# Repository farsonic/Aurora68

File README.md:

# Aurora68

A Raspberry Pi on a PiStorm in a compact Macintosh's 68000 socket. It runs Emu68 and boots Apple's Macintosh
IIci ROM, so the SE becomes a 68040-class Mac with up to 128 MB of memory, while its own screen, keyboard, mouse,
floppy and SCSI keep working. On top it adds a colour second screen and stereo sound over HDMI, disk images on the
SD card, WiFi, Ethernet, Bluetooth and USB keyboards and mice, USB sticks and a remote control, through a NuBus
card that exists only in software.

- **Macs:** the SE; the Plus, 512Ke, 512K and 128K with `mac.board=plus|512ke|512k|128k`.
- **Systems:** System 7.1 and System 6.0.8 tested. A/UX 3.1.1 runs on a real SE with the experimental 68030 MMU
  (`mac.mmu=full`), with Bluetooth and USB input, networking over the Pi's WiFi and the HDMI screen: see
  `docs/25-aux-handover.md`.
- **Hardware:** a classic PiStorm (the DIP-64 Amiga board) with a Raspberry Pi 3A+ or Zero 2 W (they fit), or a
  3B/3B+ (overhangs), and a microSD card with a FAT32 first partition.
- **You supply:** your own Macintosh IIci ROM (368CADFE, 512 KB) and Mac system software. Nothing of Apple's is
  included.

## Quick start

1. Unzip the latest release from the Releases page onto the card's root.
2. Copy your IIci ROM there as `MacIIci_368CADFE.rom`.
3. In the card's root (macOS or Linux, needs `curl` and `python3`), run this one line. It fetches the Pi's boot
   files and every Pi model's WiFi and Bluetooth firmware, checks them, and builds the container `aurora68.cpio`:

   ```bash
   sh get-firmware.sh --container MacIIci_368CADFE.rom --declrom aurora68-se.declrom
   ```

4. Put the card in the Pi, the PiStorm in the 68000 socket (pin 1 at the notch end), plug in an HDMI monitor if
   you have one, and switch on. `cmdline.txt` as shipped is ready for an SE:

   ```
   enable_cache debug mac.board=se bt.pair=1 mac.console=hdmi
   ```

The Mac starts from its own SCSI disk (or a BlueSCSI), a floppy, or a disk image (`.img`, `.hda`, `.dsk`) in the
card's root. The Aurora68 programs come on `Aurora68-Apps.img`, which the Mac mounts as the disk "Aurora68" beside
your startup disk; the drivers need no installing.
`READ-ME-FIRST.txt` in the zip says what the first start should look like.

## More

- `docs/guide.md`: the full guide. Every `cmdline.txt` option, `config.txt` and HDMI sizes, disks and SCSI images,
  the other Macs, the remote control, Setup and Recovery, larger startup disks, the hardware table.
- `RELEASE-NOTES.md`: what is new, and what has been checked on real hardware.
- `docs/00-overview.md`: the story of the project, with links to the working documents.
- `CLAUDE.md`: building everything from source and running the QEMU/MAME testbed.

## Licences

The Emu68 fork is MPL-2.0, the Alice68 modules in `emu68/src/alice/` are GPL-2.0-only, and the Macintosh side,
tools and documents are MPL-2.0. Third-party code compiled into the kernel (minimp3, dr_flac, stb_vorbis) and the
radio stations Aurora68 Play lists are credited in `docs/guide.md`, "Licences". Apple ROMs, system software and
Broadcom's firmware are not distributed.

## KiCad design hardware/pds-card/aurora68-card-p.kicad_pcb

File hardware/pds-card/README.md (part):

<!-- SPDX-License-Identifier: MPL-2.0 -->
# Aurora68 Card P: a Raspberry Pi 3A+ in the Macintosh SE's processor direct slot

*24 November 2026, first draft; reworked twice on 25 November 2026 (first the CPLD beside the Pi's header, the Pi 3B/3B+ keep-out
widened, 3D models; then the Pi beside the slot plug, with the CPLD, latches and switches between;
the owner's 30 mm blower on a Raspberry Pi 5-style fan header; /BR held and stock mode from the Interrupt switch, after
the MicroMac Performer).* A KiCad 8 design for **Card P** of docs/22 section 5.1: a card for the SE's 96-pin
processor direct slot (PDS) that carries a Raspberry Pi 3A+ on its 40-pin header and does what the classic PiStorm
does in the 68000's socket, through the slot instead. The SE's own 68000 stays in its socket; the card takes the
bus from it with /BR, /BG and /BGACK and can hand it back ("stock mode"). The Pi runs Aurora68's kernel unchanged:
the card speaks the classic PiStorm's GPIO protocol (`PROTOCOL.md`). The bus half (CPLD, latches, bus switches,
power, slot plug) and the Pi now sit together in the right-hand 80 mm of the card, beside the slot plug; a Compute
Module card (Card M) would reuse that corner with a module in the Pi's place.

## Status: a draft for a hardware designer to review

- **Not reviewed** by anyone who builds hardware. **Not built.** **KiCad's ERC and DRC have not been run**: KiCad
  is not installed where the files were made. They were generated by Python from `tools/design.py`, read back
  and checked by `tools/validate.py` (below), which is no substitute.
- **Four layers since 25 November 2026, and not fully routed** (see "Routing"): Freerouting leaves 40 connections open in 25 nets (the data latches' slot side, SE_D1-D15; nine of the Pi's data lines to the latches; two latch strobes); the
  copper is a starting point for a person.
- **The CPLD logic is simulated, not synthesised**: Icarus Verilog against a behavioural SE, 1608 checks pass and
  four deliberately broken copies fail (`rtl/README.md`); Quartus has not fitted it, so whether it fits an EPM240 is
  an estimate (145 LUTs and 117 flip-flops by yosys: probably yes; the board takes an EPM570 in the same footprint).
- Several mechanical facts are our reading of Apple's drawings and need a real SE with its chassis and a ruler:
  the height limit's direction, the plug's exact position, the Pi's stack (sections below).

## What is on the card

| Ref | Part | Why |
|---|---|---|
| J1 | 96-pin DIN 41612 type C plug, male, straight, press-fit, **on the underside** | the slot (Apple, *Designing Cards and Drivers*, 3rd ed., Figure 17-4) |
| U1 | EPM240T100C5N (or EPM570T100C5N), as the PiStorm | the bus cycle, arbitration, stock mode, fan, status (`rtl/aurora68_pds.v`) |
| U2-U5 | 74LVC16373 x4, as the PiStorm | address (A1-A23) and data latches, write and read, 5 V tolerant |
| U6, U7 | SN74CBTD3384 x2, as the PiStorm | the strobes, function codes, /DTACK, /VPA, /BERR, E, /VMA, interrupts, /RESET and the arbitration lines between the slot and the CPLD (one channel spare since /PMCYC went) |
| U8 | AMS1117-3.3 (the PiStorm's LM1117-3.3) | 3.3 V for the CPLD and latches |
| F1, U9 | 1.1 A polyfuse, LM66100 ideal diode | the slot's +5 V to the Pi and the card; a Pi also powered from its own USB never feeds the SE |
| J2 | 2x20 socket, 6.0 mm | the Pi 3A+ (or Zero 2 W), plugged in components-down |
| J3, R8, D1, R6, F2 | JST-SH 4-pin fan header (SM04B-SRSS-TB) wired as the Raspberry Pi 5's FAN connector, 100 ohm from the CPLD's PWM pin, a BAT54C holding PWM and TACH at 3.3 V, the tachometer pull-up, a 0.35 A polyfuse | docs/22 section 6; section "The fan" |
| M1 | the owner's 30 x 30 x 7 mm 5 V blower, optional, on three M2 screws | section "The fan" |
| J4, F3, R11 | 10-way 1.0 mm FFC connector, 0.75 A polyfuse | the cable to a connector card at the rear (Apple's Figures 17-2, 17-7, 17-8): USB, +5 V for it, an LED |
| J5 | 4-pin header | USB from the Pi 3A+'s USB-A socket (a short pigtail with a **right-angle** plug, its cable towards the rear: section "The fan"), on to J4. Its VBUS pin is deliberately not connected |
| D2, R10 | LED | activity |
| R1-R5, C1-C16 | as the PiStorm where it has them | JTAG pull-ups (4.7 k on TMS and TDI), 22 ohm on the 68000 clock C8M (R3), the SE power sense (10 k / 15 k), decoupling |
| R12 | 22 ohm | GPCLK0's series resistor at the source, beside the Pi's pin 7 (new on 25 November) |
| H1, H2 | 3.86 mm holes | Apple's card supports (Figure 17-1) |
| H3-H8 | M2.5 holes | the Pi's standoffs (3A+: four; Zero 2 W: two more) |

The full list with values, LCSC numbers where known, heights and notes is `bom.csv`. The netlist is the
schematic: `aurora68-card-p.kicad_sch` and its five sheets (slot and bus switches, CPLD and latches, Pi socket,
power, fan/LED/rear cable), pictured in `img/sch-*.png`. There is no stock-mode jumper any more: stock mode is
entered with the SE's own Interrupt switch held through a reset (section "Arbitration and stock mode").

## How it follows the PiStorm, and where it departs

The owner's rule for Card P: as simple and as close to the PiStorm Rev B as possible, cheap to make. So the
circuit is the Rev B's (reference/pistorm: `Pistorm_Rev_B-1.pdf`, the Altium files, the BOM): the same CPLD family
and package wired the same way for an EPM240 or EPM570, the same four 74LVC16373 latches, the same two CBTD3384
bus switches carrying the same 68000 control signals, the 22 ohm resistor on the CPU clock, the 3.3 V LDO with
22 uF in and out, 4.7 k pull-ups on TMS and TDI, 100 nF per IC, the Pi's GPIO 0-27 used exactly as there, the Pi
plugged in components-down over the card as it hangs over the logic board on a PiStorm, and **every CPLD pin of
every signal the PiStorm has on the PiStorm's own pin number** (`rtl/aurora68_pds.qsf`, checked against the Rev B's
`pistorm.qsf`; the Pi header's nets checked against the Rev B schematic by reading its Altium file). Departures,
each for a reason:

| # | Departure | Reason |
|---|---|---|
| 1 | A 96-pin DIN plug on the underside instead of the 68000 DIP-64 plug | the slot |
| 2 | CPLD pin 53 (E) is an input, 71 (/BG) an input, 69 (/BR) and 70 (/BGACK) open-drain outputs; 68 (the PiStorm's /HALT), 51, 99, 100 (CLK_SEL, C1, C3) unused; new: 77 SE power sense, 78 fan PWM, 81 tachometer, 83 LED | the slot card's roles are the other way round: the 68000 is still there, so the card requests the bus instead of granting it and follows the 68000's E; on the SE /HALT is /RESET, so its pin is free |
| 3 | The read timing needs **transparent** latches (74LVC16373) | the new cycle opens the read latch on /DTACK and closes it where a 68000 latches (docs/18 C2). Note: the Rev B BOM in reference/pistorm lists SN74LVC16374 (edge-triggered) although the archive is named "..._74LVC16373": with a '16374 this card would latch at the wrong edge |
| 4 | +5 V through a polyfuse and an LM66100 ideal diode (the PiStorm takes the socket's 5 V straight) | the brief: a Pi on its own USB must not back-feed the SE. A Schottky is simpler but drops 0.35-0.45 V at the Pi's current, putting a Pi 3A+ at or under its 4.63 V under-voltage threshold on an old SE supply (docs/12, "Power through the socket"); a single P-MOSFET with its gate grounded blocks reverse polarity but conducts both ways once on, so it does not stop back-feeding. The LM66100 is one SC-70 part |
| 5 | CBTD3384 VCC from the protected 5 V (5V_PI) | the switches must be off when the card is unpowered, and powered whenever the CPLD is |
| 6 | VCCINT tied to 3.3 V directly | the PiStorm links it through a 0 ohm resistor beside an unfitted 1.8 V regulator option; only MAX II "G" parts would need it |
| 7 | 0603 resistors and capacitors, 0805 for 10 and 22 uF (the PiStorm uses 0402 and 0603) | the owner's assembly preference |
| 8 | Added: the SE power sense (2 resistors), the fan header (wired as a Raspberry Pi 5's: no driver, PWM straight from the CPLD), the FFC to the rear connector card with its fuse, the USB-in header, the activity LED | docs/22 sections 4 and 6 |
| 9 | Not a departure from the PiStorm but from the brief: the slot's control signals reach the CPLD through the CBTD3384 switches, not through 74LVC buffers | the owner's rule. Apple asks for buffering when a card loads a line with more than two 74LS inputs and 30 pF, or more than about 2 inches of trace. Each control line here sees one CMOS input (the CPLD, about 10 pF and 10 uA), the switch (10-12 pF on) and the track on both sides of the switch: a few uA of DC load against two LS loads' 40 uA / 0.8 mA, but a capacitance close to Apple's 30 pF (section "Placement" has the routed figures; on four layers a 0.15 mm track 0.21 mm over its plane is about 0.07 pF/mm). 74LVC buffers near J1 are the remedy if a reviewer or a scope says so. Address and data go through the latches, which are real buffers. The CBTD's level shifting brings 5 V signals down to about 4.3 V at the CPLD (the PiStorm runs that way; the MAX II's absolute maximum input is 4.6 V) |
| 10 | R12, 22 ohm in series with GPCLK0 (GPIO 4) at the Pi's pin | asked for with the placement rework: source termination for the 200 MHz clock. The PiStorm wires GPIO 4 straight to the CPLD; fit 0 ohm to match it. It is the only schematic change of the rework |
| 11 | The CPLD, two latches and both switches sit under the Pi, the Pi beside the slot plug | as on the PiStorm, where the Pi sits over the CPLD and latches: short Pi-speed lines and short SE lines (section "Placement") |
| 13 | Four layers (the PiStorm has two): L1 signals, L2 ground, L3 3.3 V, L4 signals | the owner's choice on 25 November 2026, after two layers left some 50 connections the router could not make: "I don't mind 4 layer if it is simpler to route and produce" (section "The board") |
| 12 | The card holds /BR for as long as it owns the bus, and stock mode is entered with the SE's Interrupt switch held through a reset; /PMCYC is not connected | the MicroMac Performer, a shipped card that took the bus from this slot, worked that way (docs/22 section 10); it removed a jumper and its pull-up (section "Arbitration and stock mode") |
0.4 pF/cm for a 0.15 mm trace over the ground pour, so some 7 pF, plus the switch's 10-12 pF and the CPLD pin's 8-10
pF, about 25-30 pF in all against Apple's 30 pF (C8M, with 20 pF allowed and no switch, sees about 16 pF). That is at
the limit: the reviewer's to confirm, with 74LVC buffers near J1 as the remedy (section "Placement"). Address and data go through the latches, which are real buffers. The CBTD's level shifting brings 5 V signals down to about 4.3 V at the CPLD (the PiStorm runs that way; the MAX II's absolute maximum input is 4.6 V) |

## Placement (25 November 2026)

**The rule this follows.** On the PiStorm the latches sit on the Pi's data bus and their strobes are combinational
copies of the Pi's write and read strobes, so the latches, as well as the CPLD, run at Pi speed; their other side is
the 68000's bus. The first draft put the CPLD and latches by the slot plug, far from the Pi; the 25 November rework
put the CPLD by the Pi, and the Pi-speed lines to the latches grew to 26 cm. With the Pi itself beside the slot plug
both sides are short, with no extra parts. So:

- **The Pi 3A+ sits beside J1**, components down on its socket as before, its microSD end (u = 0) at x = 198.7: as
  close to J1 as its standoffs allow (its u = 3.5 holes end at x = 197.95, J1's courtyard starts at 198.04; further
  right they would land in J1's pin field). It covers x 133.7-198.7, y 53.2-109.2.
- **Turned over about its short axis** this time, so that a 3B/3B+'s USB and RJ45 and their plugs reach away from
  J1, to the empty left of the card: its header now runs along the Pi's **rear** edge (y 55.4/58.0, x 142.1-190.3)
  and its USB socket faces left.
- **The cost of that turn: the HDMI and audio jacks now overhang the card's front edge.** They stand 1.4 and 2.5
  mm past the Pi's own edge (Raspberry Pi's drawing), and the Pi's front edge is at y 109.2 because its rear edge
  cannot come forward of y 53.2 (there Apple's slope allows 9.91 mm and the Pi's back is at 9.90). So the audio jack
  stands 1.6 mm, the HDMI socket 0.5 mm and the micro-USB socket 0.2 mm past Apple's outline at the front, at 2.0 to
  8.5 mm above the card. The alternative, the jacks inside the outline, puts the Pi's rear edge at y 51.6 and its back
  0.15 mm over the slope. Nothing else changes between the two; the owner should choose after measuring what is in
  front of the card's edge in a real SE (the logic board's front part, the SIMMs). `validate.py` reports it as warning
  9e. The HDMI socket now faces the front of the machine, so it is no use for a second screen without a short
  right-angle adaptor, and was no more reachable before.
- **The cluster between the Pi's header and J1, as tight as the PiStorm's:**
  - U1, the EPM240, under the Pi in the pocket between the keep-outs under its USB socket and its SoC (x 146.8-164.1,
    y 60.2-77.5), rotated 180 degrees so its Pi pins face the header and pin 12 (GPCLK0) faces the Pi's pin 7. Its
    decoupling, the JTAG pull-ups and R12 sit beside it, under the Pi.
  - U2 (A1-A15) and the two CBTD3384 switches, U6 and U7, under the Pi in the column between its SoC and display
    connector keep-outs (x 180.8-190.2), right beside J1's address and control pins. U6 carries E, the interrupts,
    /BERR, /RESET, /AS, /UDS, /LDS (its seventh channel is spare); U7 R/W, /DTACK, the arbitration lines, /VMA, /VPA and the function codes,
    each switch by the plug pins it serves.
  - U3 (A16-A23), U4 and U5 (the data, write and read) behind the Pi's header (y 38.5-51.5), by J1's upper address
    and data pins.
  - The power path (F1, the LM66100, the LDO, F2, F3, R4/R5) in the strip behind them along the rear (y 22-34), the
    5 V reaching the Pi's 5 V pins a few cm away.
- **The rest:** the blower M1 left of the Pi with its outlet towards it, its JST-SH header J3 (with R8, D1, R6)
  behind it, all outside the 3B zone but the fan itself (section "The fan"); USB-in J5 behind the 3B zone; the FFC J4
  where Apple suggests the cable connector (rear middle); the LED by it. The card keeps its full length for Apple's
  support holes; its left 68 mm hold nothing but the holes.

**Lengths and loading (25 November 2026).** Straight lines, from the placement alone: GPCLK0 22.9 mm (J2 pin 7,
R12, the CPLD's pin 12); every Pi-to-CPLD net 27 mm or less; the Pi's data bus from its socket to the farthest latch
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
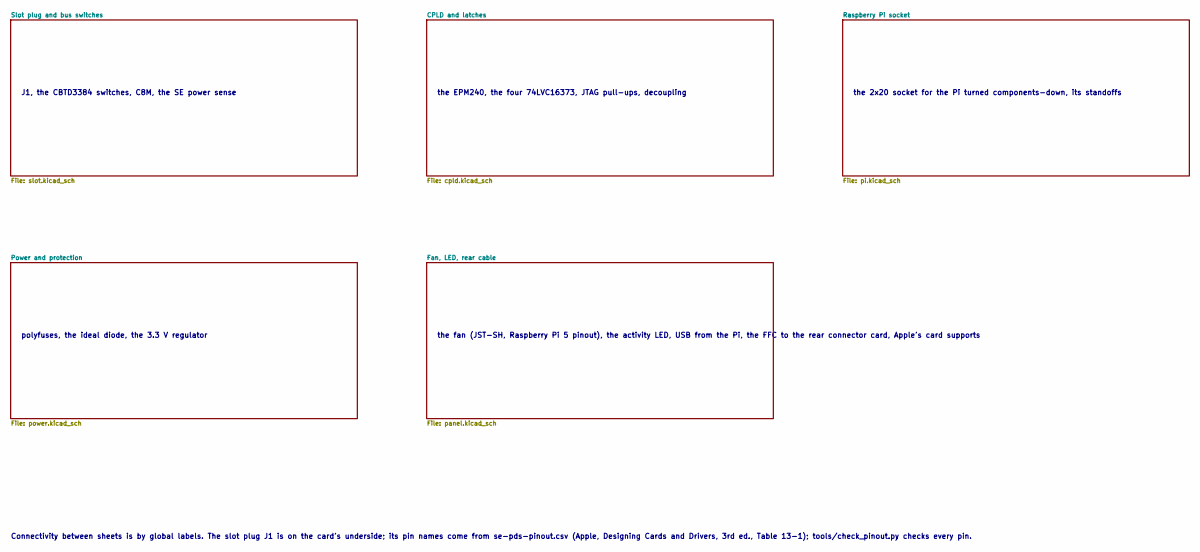
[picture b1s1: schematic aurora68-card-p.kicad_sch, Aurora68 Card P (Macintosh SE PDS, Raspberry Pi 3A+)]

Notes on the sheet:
J1, the CBTD3384 switches, C8M, the SE power sense
the EPM240, the four 74LVC16373, JTAG pull-ups, decoupling
the 2x20 socket for the Pi turned components-down, its standoffs
polyfuses, the ideal diode, the 3.3 V regulator
the fan (JST-SH, Raspberry Pi 5 pinout), the activity LED, USB from the Pi, the FFC to the rear connector card, Apple's card supports
Connectivity between sheets is by global labels. The slot plug J1 is on the card's underside; its pin names come from se-pds-pinout.csv (Apple, Designing Cards and Drivers, 3rd ed., Table 13-1); tools/check_pinout.py checks every pin.

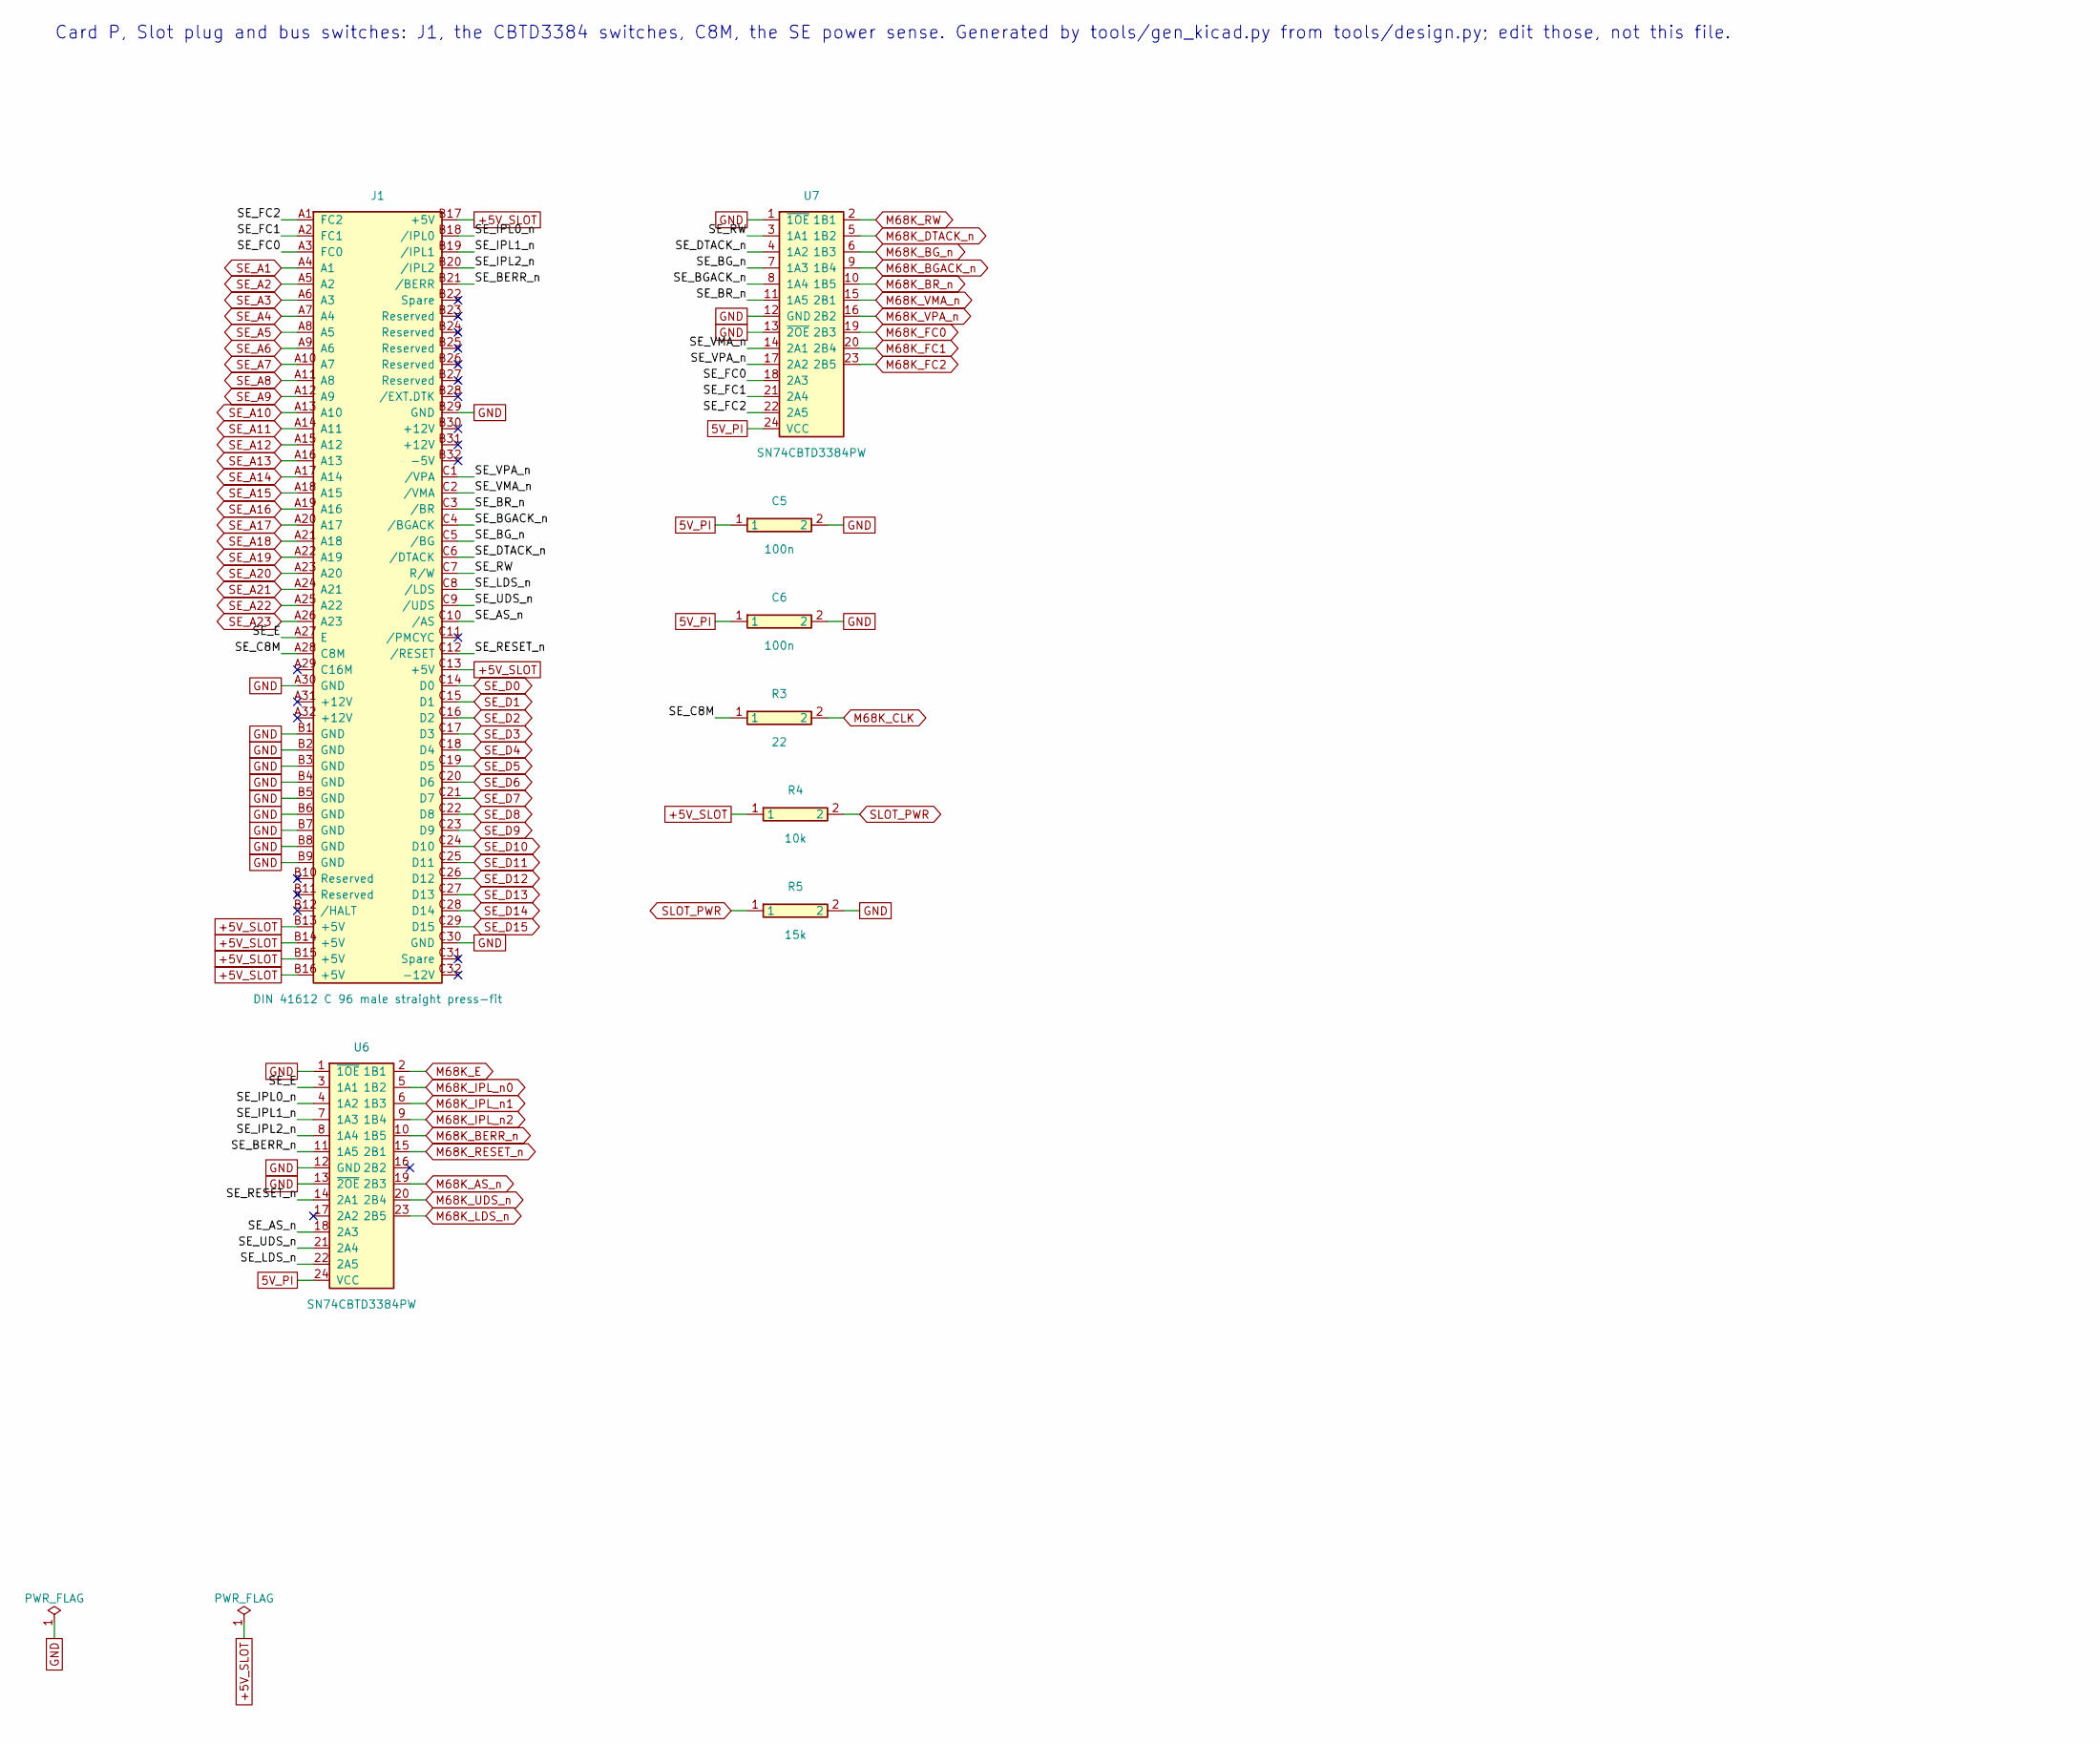
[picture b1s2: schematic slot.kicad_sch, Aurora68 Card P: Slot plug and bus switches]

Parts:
C5, C6: 100n; C_0603_1608Metric; LCSC C14663
J1: DIN 41612 C 96 male straight press-fit; Aurora68_DIN41612_C_3x32_Male_Straight_PressFit_Bottom; MPN DIN 41612 type C, 3x32 (a+b+c), male, s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
R3: 22; R_0603_1608Metric; LCSC C23345
R4: 10k; R_0603_1608Metric; LCSC C25804
R5: 15k; R_0603_1608Metric; LCSC C22809
U6, U7: SN74CBTD3384PW; TSSOP-24_4.4x7.8mm_P0.65mm; MPN SN74CBTD3384PWR; LCSC C7155

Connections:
5V_PI: C5.1, C6.1, U6.24, U7.24; also elsewhere on the board
+5V_SLOT: J1.B13, J1.B14, J1.B15, J1.B16, J1.B17, J1.C13, R4.1; also elsewhere on the board
GND: C5.2, C6.2, J1.A30, J1.B1, J1.B2, J1.B3, J1.B4, J1.B5, J1.B6, J1.B7, J1.B8, J1.B9, J1.B29, J1.C30, R5.2, U6.1, U6.12, U6.13, U7.1, U7.12, U7.13; also elsewhere on the board
M68K_AS_n: U6.19; also elsewhere on the board
M68K_BERR_n: U6.10; also elsewhere on the board
M68K_BGACK_n: U7.9; also elsewhere on the board
M68K_BG_n: U7.6; also elsewhere on the board
M68K_BR_n: U7.10; also elsewhere on the board
M68K_CLK: R3.2; also elsewhere on the board
M68K_DTACK_n: U7.5; also elsewhere on the board
M68K_E: U6.2; also elsewhere on the board
M68K_FC0: U7.19; also elsewhere on the board
M68K_FC1: U7.20; also elsewhere on the board
M68K_FC2: U7.23; also elsewhere on the board
M68K_IPL_n0: U6.5; also elsewhere on the board
M68K_IPL_n1: U6.6; also elsewhere on the board
M68K_IPL_n2: U6.9; also elsewhere on the board
M68K_LDS_n: U6.23; also elsewhere on the board
M68K_RESET_n: U6.15; also elsewhere on the board
M68K_RW: U7.2; also elsewhere on the board
M68K_UDS_n: U6.20; also elsewhere on the board
M68K_VMA_n: U7.15; also elsewhere on the board
M68K_VPA_n: U7.16; also elsewhere on the board
SE_A1: J1.A4; also elsewhere on the board
SE_A2: J1.A5; also elsewhere on the board
SE_A3: J1.A6; also elsewhere on the board
SE_A4: J1.A7; also elsewhere on the board
SE_A5: J1.A8; also elsewhere on the board
SE_A6: J1.A9; also elsewhere on the board
SE_A7: J1.A10; also elsewhere on the board
SE_A8: J1.A11; also elsewhere on the board
SE_A9: J1.A12; also elsewhere on the board
SE_A10: J1.A13; also elsewhere on the board
SE_A11: J1.A14; also elsewhere on the board
SE_A12: J1.A15; also elsewhere on the board
SE_A13: J1.A16; also elsewhere on the board
SE_A14: J1.A17; also elsewhere on the board
SE_A15: J1.A18; also elsewhere on the board
SE_A16: J1.A19; also elsewhere on the board
SE_A17: J1.A20; also elsewhere on the board
SE_A18: J1.A21; also elsewhere on the board
SE_A19: J1.A22; also elsewhere on the board
SE_A20: J1.A23; also elsewhere on the board
SE_A21: J1.A24; also elsewhere on the board
SE_A22: J1.A25; also elsewhere on the board
SE_A23: J1.A26; also elsewhere on the board
SE_AS_n: J1.C10, U6.18
SE_BERR_n: J1.B21, U6.11
SE_BGACK_n: J1.C4, U7.8
SE_BG_n: J1.C5, U7.7
SE_BR_n: J1.C3, U7.11
SE_C8M: J1.A28, R3.1
SE_D0: J1.C14; also elsewhere on the board
SE_D1: J1.C15; also elsewhere on the board
SE_D2: J1.C16; also elsewhere on the board
SE_D3: J1.C17; also elsewhere on the board
SE_D4: J1.C18; also elsewhere on the board
SE_D5: J1.C19; also elsewhere on the board
SE_D6: J1.C20; also elsewhere on the board
SE_D7: J1.C21; also elsewhere on the board
SE_D8: J1.C22; also elsewhere on the board
SE_D9: J1.C23; also elsewhere on the board
SE_D10: J1.C24; also elsewhere on the board
SE_D11: J1.C25; also elsewhere on the board
SE_D12: J1.C26; also elsewhere on the board
SE_D13: J1.C27; also elsewhere on the board
SE_D14: J1.C28; also elsewhere on the board
SE_D15: J1.C29; also elsewhere on the board
SE_DTACK_n: J1.C6, U7.4
SE_E: J1.A27, U6.3
SE_FC0: J1.A3, U7.18
SE_FC1: J1.A2, U7.21
SE_FC2: J1.A1, U7.22
SE_IPL0_n: J1.B18, U6.4
SE_IPL1_n: J1.B19, U6.7
SE_IPL2_n: J1.B20, U6.8
SE_LDS_n: J1.C8, U6.22
SE_RESET_n: J1.C12, U6.14
SE_RW: J1.C7, U7.3
SE_UDS_n: J1.C9, U6.21
SE_VMA_n: J1.C2, U7.14
SE_VPA_n: J1.C1, U7.17
SLOT_PWR: R4.2, R5.1; also elsewhere on the board

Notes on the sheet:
Card P, Slot plug and bus switches: J1, the CBTD3384 switches, C8M, the SE power sense. Generated by tools/gen_kicad.py from tools/design.py; edit those, not this file.

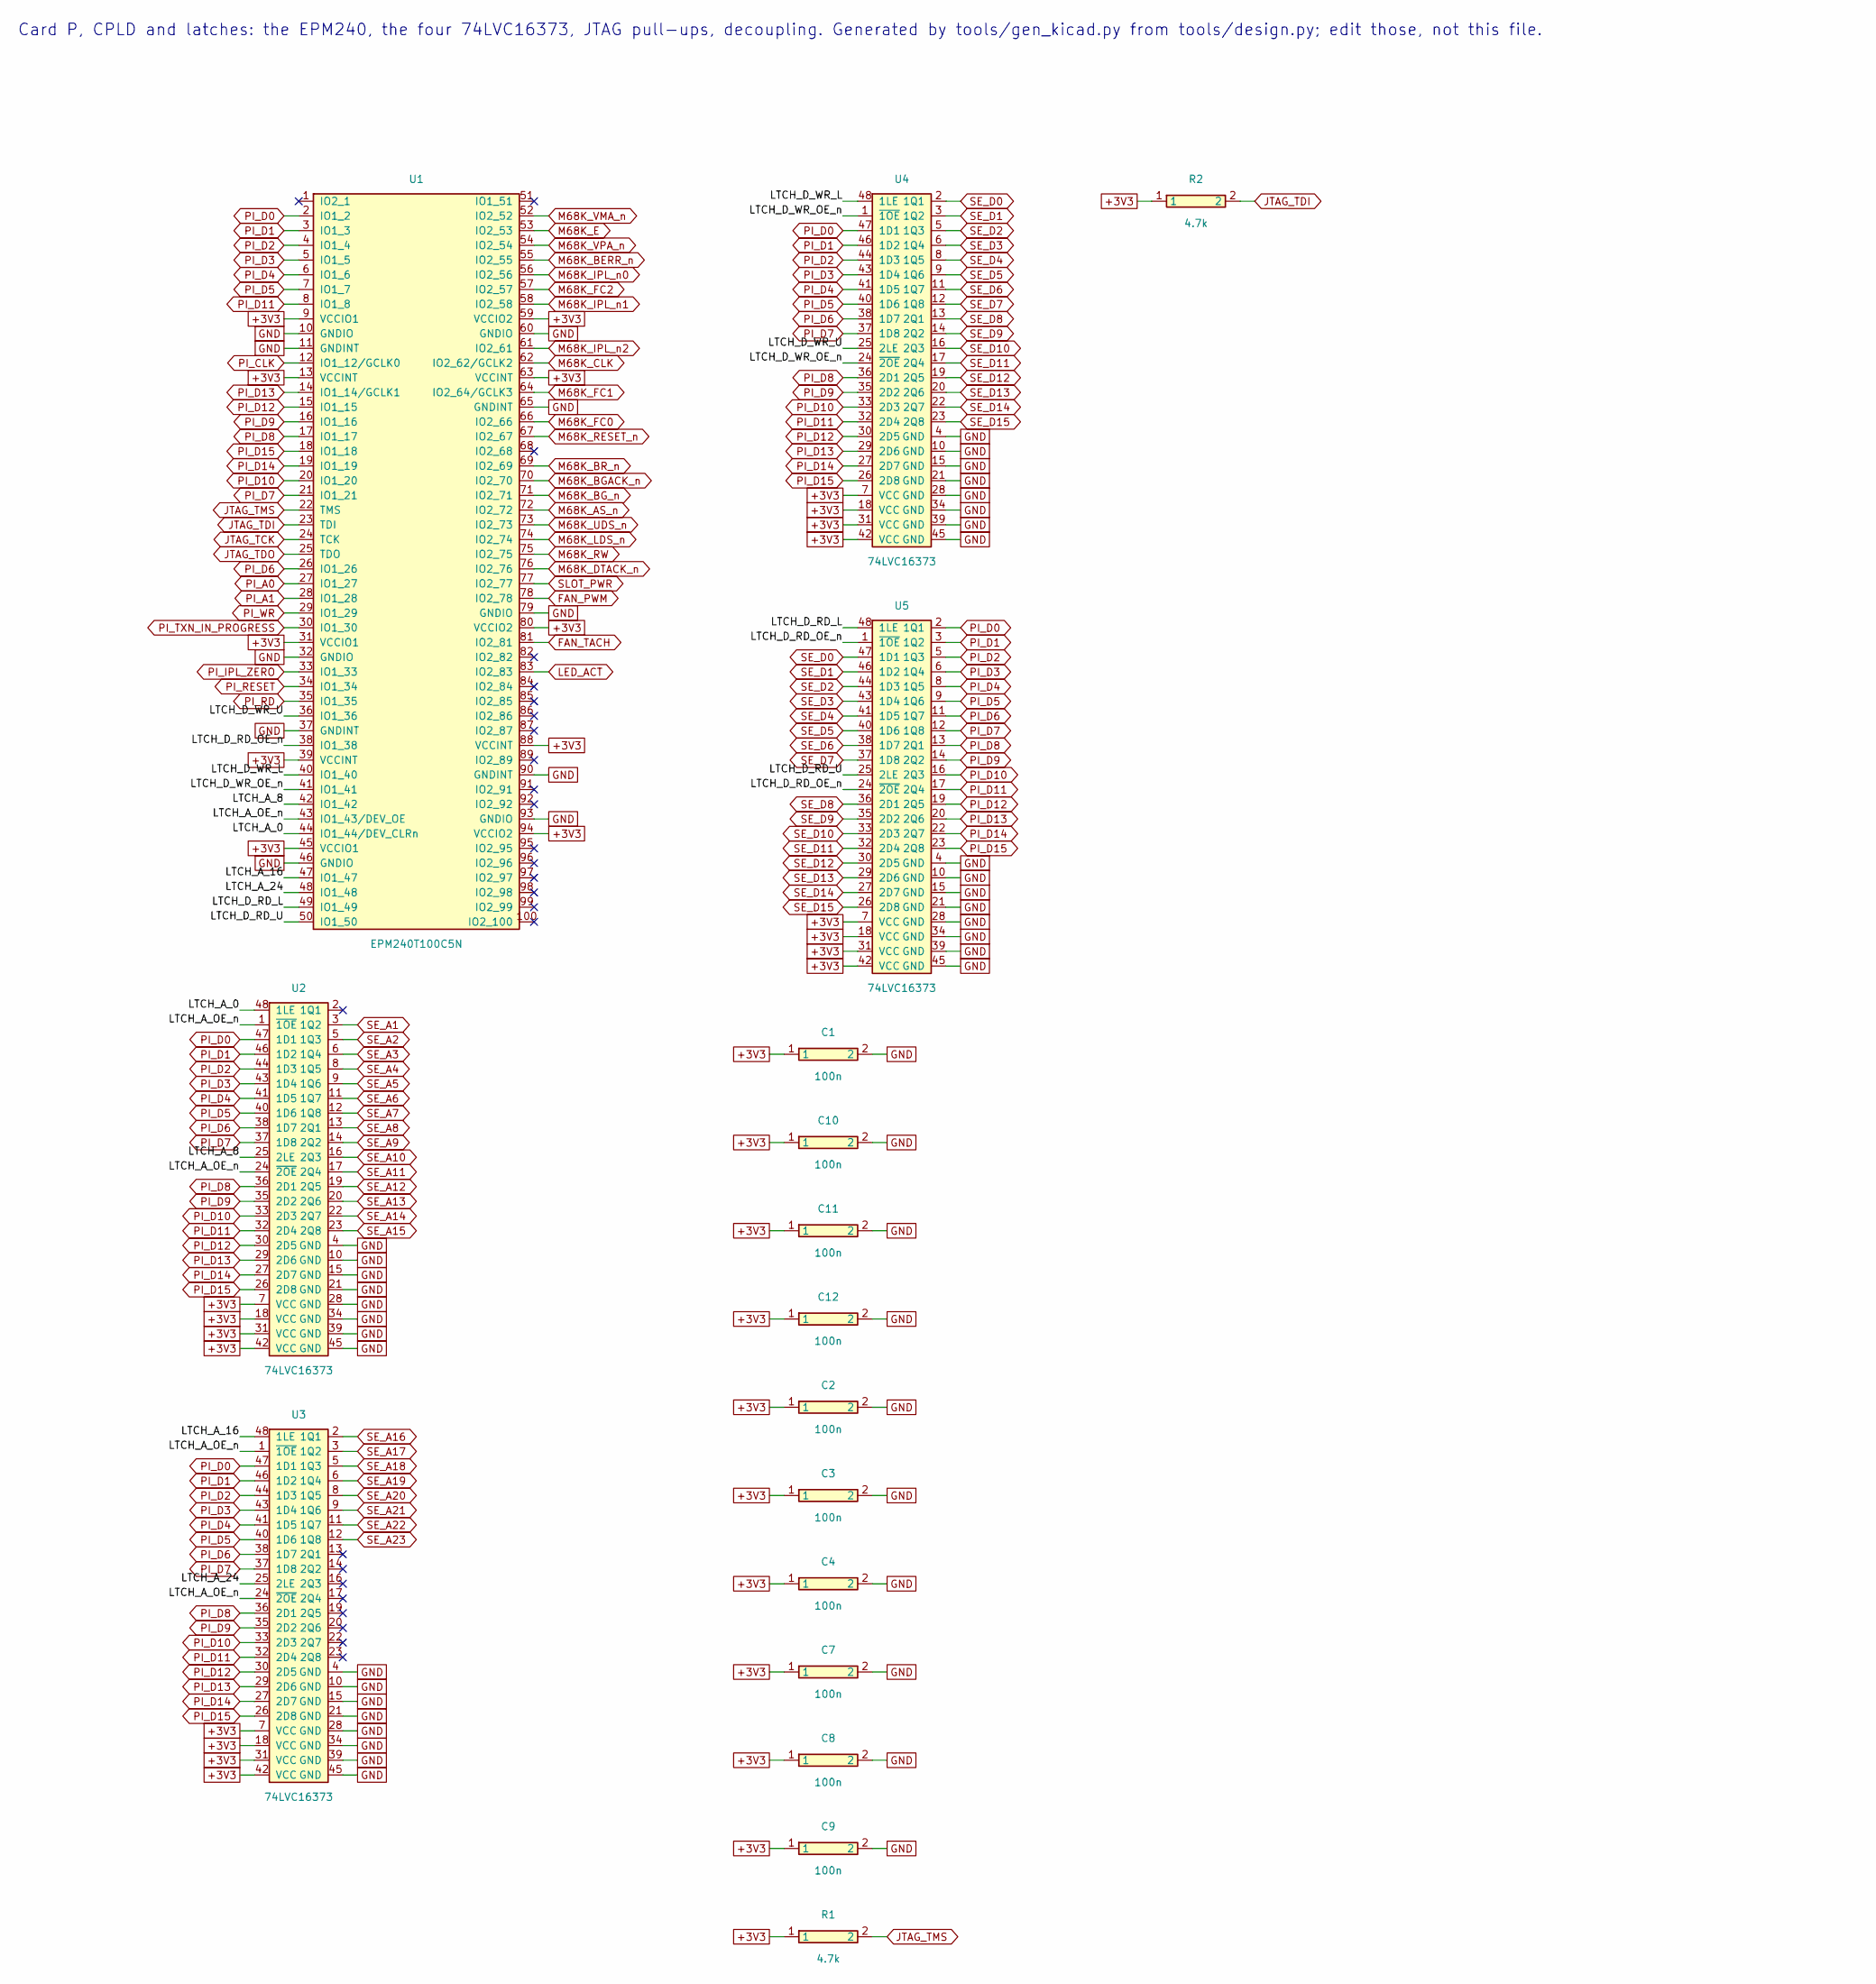
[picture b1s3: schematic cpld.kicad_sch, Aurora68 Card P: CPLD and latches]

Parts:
C1, C2, C3, C4, C7, C8, C9, C10, C11, C12: 100n; C_0603_1608Metric; LCSC C14663
R1, R2: 4.7k; R_0603_1608Metric; LCSC C23162
U1: EPM240T100C5N; TQFP-100_14x14mm_P0.5mm; MPN EPM240T100C5N (or EPM570T100C5N, LCSC C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
U2, U3, U4, U5: 74LVC16373; TSSOP-48_6.1x12.5mm_P0.5mm; MPN SN74LVC16373ADGGR

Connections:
+3V3: C1.1, C2.1, C3.1, C4.1, C7.1, C8.1, C9.1, C10.1, C11.1, C12.1, R1.1, R2.1, U1.9, U1.13, U1.31, U1.39, U1.45, U1.59, U1.63, U1.80, U1.88, U1.94, U2.7, U2.18, U2.31, U2.42, U3.7, U3.18, U3.31, U3.42, U4.7, U4.18, U4.31, U4.42, U5.7, U5.18, U5.31, U5.42; also elsewhere on the board
FAN_PWM: U1.78; also elsewhere on the board
FAN_TACH: U1.81; also elsewhere on the board
GND: C1.2, C2.2, C3.2, C4.2, C7.2, C8.2, C9.2, C10.2, C11.2, C12.2, U1.10, U1.11, U1.32, U1.37, U1.46, U1.60, U1.65, U1.79, U1.90, U1.93, U2.4, U2.10, U2.15, U2.21, U2.28, U2.34, U2.39, U2.45, U3.4, U3.10, U3.15, U3.21, U3.28, U3.34, U3.39, U3.45, U4.4, U4.10, U4.15, U4.21, U4.28, U4.34, U4.39, U4.45, U5.4, U5.10, U5.15, U5.21, U5.28, U5.34, U5.39, U5.45; also elsewhere on the board
JTAG_TCK: U1.24; also elsewhere on the board
JTAG_TDI: R2.2, U1.23; also elsewhere on the board
JTAG_TDO: U1.25; also elsewhere on the board
JTAG_TMS: R1.2, U1.22; also elsewhere on the board
LED_ACT: U1.83; also elsewhere on the board
LTCH_A_0: U1.44, U2.48
LTCH_A_8: U1.42, U2.25
LTCH_A_16: U1.47, U3.48
LTCH_A_24: U1.48, U3.25
LTCH_A_OE_n: U1.43, U2.1, U2.24, U3.1, U3.24
LTCH_D_RD_L: U1.49, U5.48
LTCH_D_RD_OE_n: U1.38, U5.1, U5.24
LTCH_D_RD_U: U1.50, U5.25
LTCH_D_WR_L: U1.40, U4.48
LTCH_D_WR_OE_n: U1.41, U4.1, U4.24
LTCH_D_WR_U: U1.36, U4.25
M68K_AS_n: U1.72; also elsewhere on the board
M68K_BERR_n: U1.55; also elsewhere on the board
M68K_BGACK_n: U1.70; also elsewhere on the board
M68K_BG_n: U1.71; also elsewhere on the board
M68K_BR_n: U1.69; also elsewhere on the board
M68K_CLK: U1.62; also elsewhere on the board
M68K_DTACK_n: U1.76; also elsewhere on the board
M68K_E: U1.53; also elsewhere on the board
M68K_FC0: U1.66; also elsewhere on the board
M68K_FC1: U1.64; also elsewhere on the board
M68K_FC2: U1.57; also elsewhere on the board
M68K_IPL_n0: U1.56; also elsewhere on the board
M68K_IPL_n1: U1.58; also elsewhere on the board
M68K_IPL_n2: U1.61; also elsewhere on the board
M68K_LDS_n: U1.74; also elsewhere on the board
M68K_RESET_n: U1.67; also elsewhere on the board
M68K_RW: U1.75; also elsewhere on the board
M68K_UDS_n: U1.73; also elsewhere on the board
M68K_VMA_n: U1.52; also elsewhere on the board
M68K_VPA_n: U1.54; also elsewhere on the board
PI_A0: U1.27; also elsewhere on the board
PI_A1: U1.28; also elsewhere on the board
PI_CLK: U1.12; also elsewhere on the board
PI_D0: U1.2, U2.47, U3.47, U4.47, U5.2; also elsewhere on the board
PI_D1: U1.3, U2.46, U3.46, U4.46, U5.3; also elsewhere on the board
PI_D2: U1.4, U2.44, U3.44, U4.44, U5.5; also elsewhere on the board
PI_D3: U1.5, U2.43, U3.43, U4.43, U5.6; also elsewhere on the board
PI_D4: U1.6, U2.41, U3.41, U4.41, U5.8; also elsewhere on the board
PI_D5: U1.7, U2.40, U3.40, U4.40, U5.9; also elsewhere on the board
PI_D6: U1.26, U2.38, U3.38, U4.38, U5.11; also elsewhere on the board
PI_D7: U1.21, U2.37, U3.37, U4.37, U5.12; also elsewhere on the board
PI_D8: U1.17, U2.36, U3.36, U4.36, U5.13; also elsewhere on the board
PI_D9: U1.16, U2.35, U3.35, U4.35, U5.14; also elsewhere on the board
PI_D10: U1.20, U2.33, U3.33, U4.33, U5.16; also elsewhere on the board
PI_D11: U1.8, U2.32, U3.32, U4.32, U5.17; also elsewhere on the board
PI_D12: U1.15, U2.30, U3.30, U4.30, U5.19; also elsewhere on the board
PI_D13: U1.14, U2.29, U3.29, U4.29, U5.20; also elsewhere on the board
PI_D14: U1.19, U2.27, U3.27, U4.27, U5.22; also elsewhere on the board
PI_D15: U1.18, U2.26, U3.26, U4.26, U5.23; also elsewhere on the board
PI_IPL_ZERO: U1.33; also elsewhere on the board
PI_RD: U1.35; also elsewhere on the board
PI_RESET: U1.34; also elsewhere on the board
PI_TXN_IN_PROGRESS: U1.30; also elsewhere on the board
PI_WR: U1.29; also elsewhere on the board
SE_A1: U2.3; also elsewhere on the board
SE_A2: U2.5; also elsewhere on the board
SE_A3: U2.6; also elsewhere on the board
SE_A4: U2.8; also elsewhere on the board
SE_A5: U2.9; also elsewhere on the board
SE_A6: U2.11; also elsewhere on the board
SE_A7: U2.12; also elsewhere on the board
SE_A8: U2.13; also elsewhere on the board
SE_A9: U2.14; also elsewhere on the board
SE_A10: U2.16; also elsewhere on the board
SE_A11: U2.17; also elsewhere on the board
SE_A12: U2.19; also elsewhere on the board
SE_A13: U2.20; also elsewhere on the board
SE_A14: U2.22; also elsewhere on the board
SE_A15: U2.23; also elsewhere on the board
SE_A16: U3.2; also elsewhere on the board
SE_A17: U3.3; also elsewhere on the board
SE_A18: U3.5; also elsewhere on the board
SE_A19: U3.6; also elsewhere on the board
SE_A20: U3.8; also elsewhere on the board
SE_A21: U3.9; also elsewhere on the board
SE_A22: U3.11; also elsewhere on the board
SE_A23: U3.12; also elsewhere on the board
SE_D0: U4.2, U5.47; also elsewhere on the board
SE_D1: U4.3, U5.46; also elsewhere on the board
SE_D2: U4.5, U5.44; also elsewhere on the board
SE_D3: U4.6, U5.43; also elsewhere on the board
SE_D4: U4.8, U5.41; also elsewhere on the board
SE_D5: U4.9, U5.40; also elsewhere on the board
SE_D6: U4.11, U5.38; also elsewhere on the board
SE_D7: U4.12, U5.37; also elsewhere on the board
SE_D8: U4.13, U5.36; also elsewhere on the board
SE_D9: U4.14, U5.35; also elsewhere on the board
SE_D10: U4.16, U5.33; also elsewhere on the board
SE_D11: U4.17, U5.32; also elsewhere on the board
SE_D12: U4.19, U5.30; also elsewhere on the board
SE_D13: U4.20, U5.29; also elsewhere on the board
SE_D14: U4.22, U5.27; also elsewhere on the board
SE_D15: U4.23, U5.26; also elsewhere on the board
SLOT_PWR: U1.77; also elsewhere on the board

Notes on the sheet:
Card P, CPLD and latches: the EPM240, the four 74LVC16373, JTAG pull-ups, decoupling. Generated by tools/gen_kicad.py from tools/design.py; edit those, not this file.

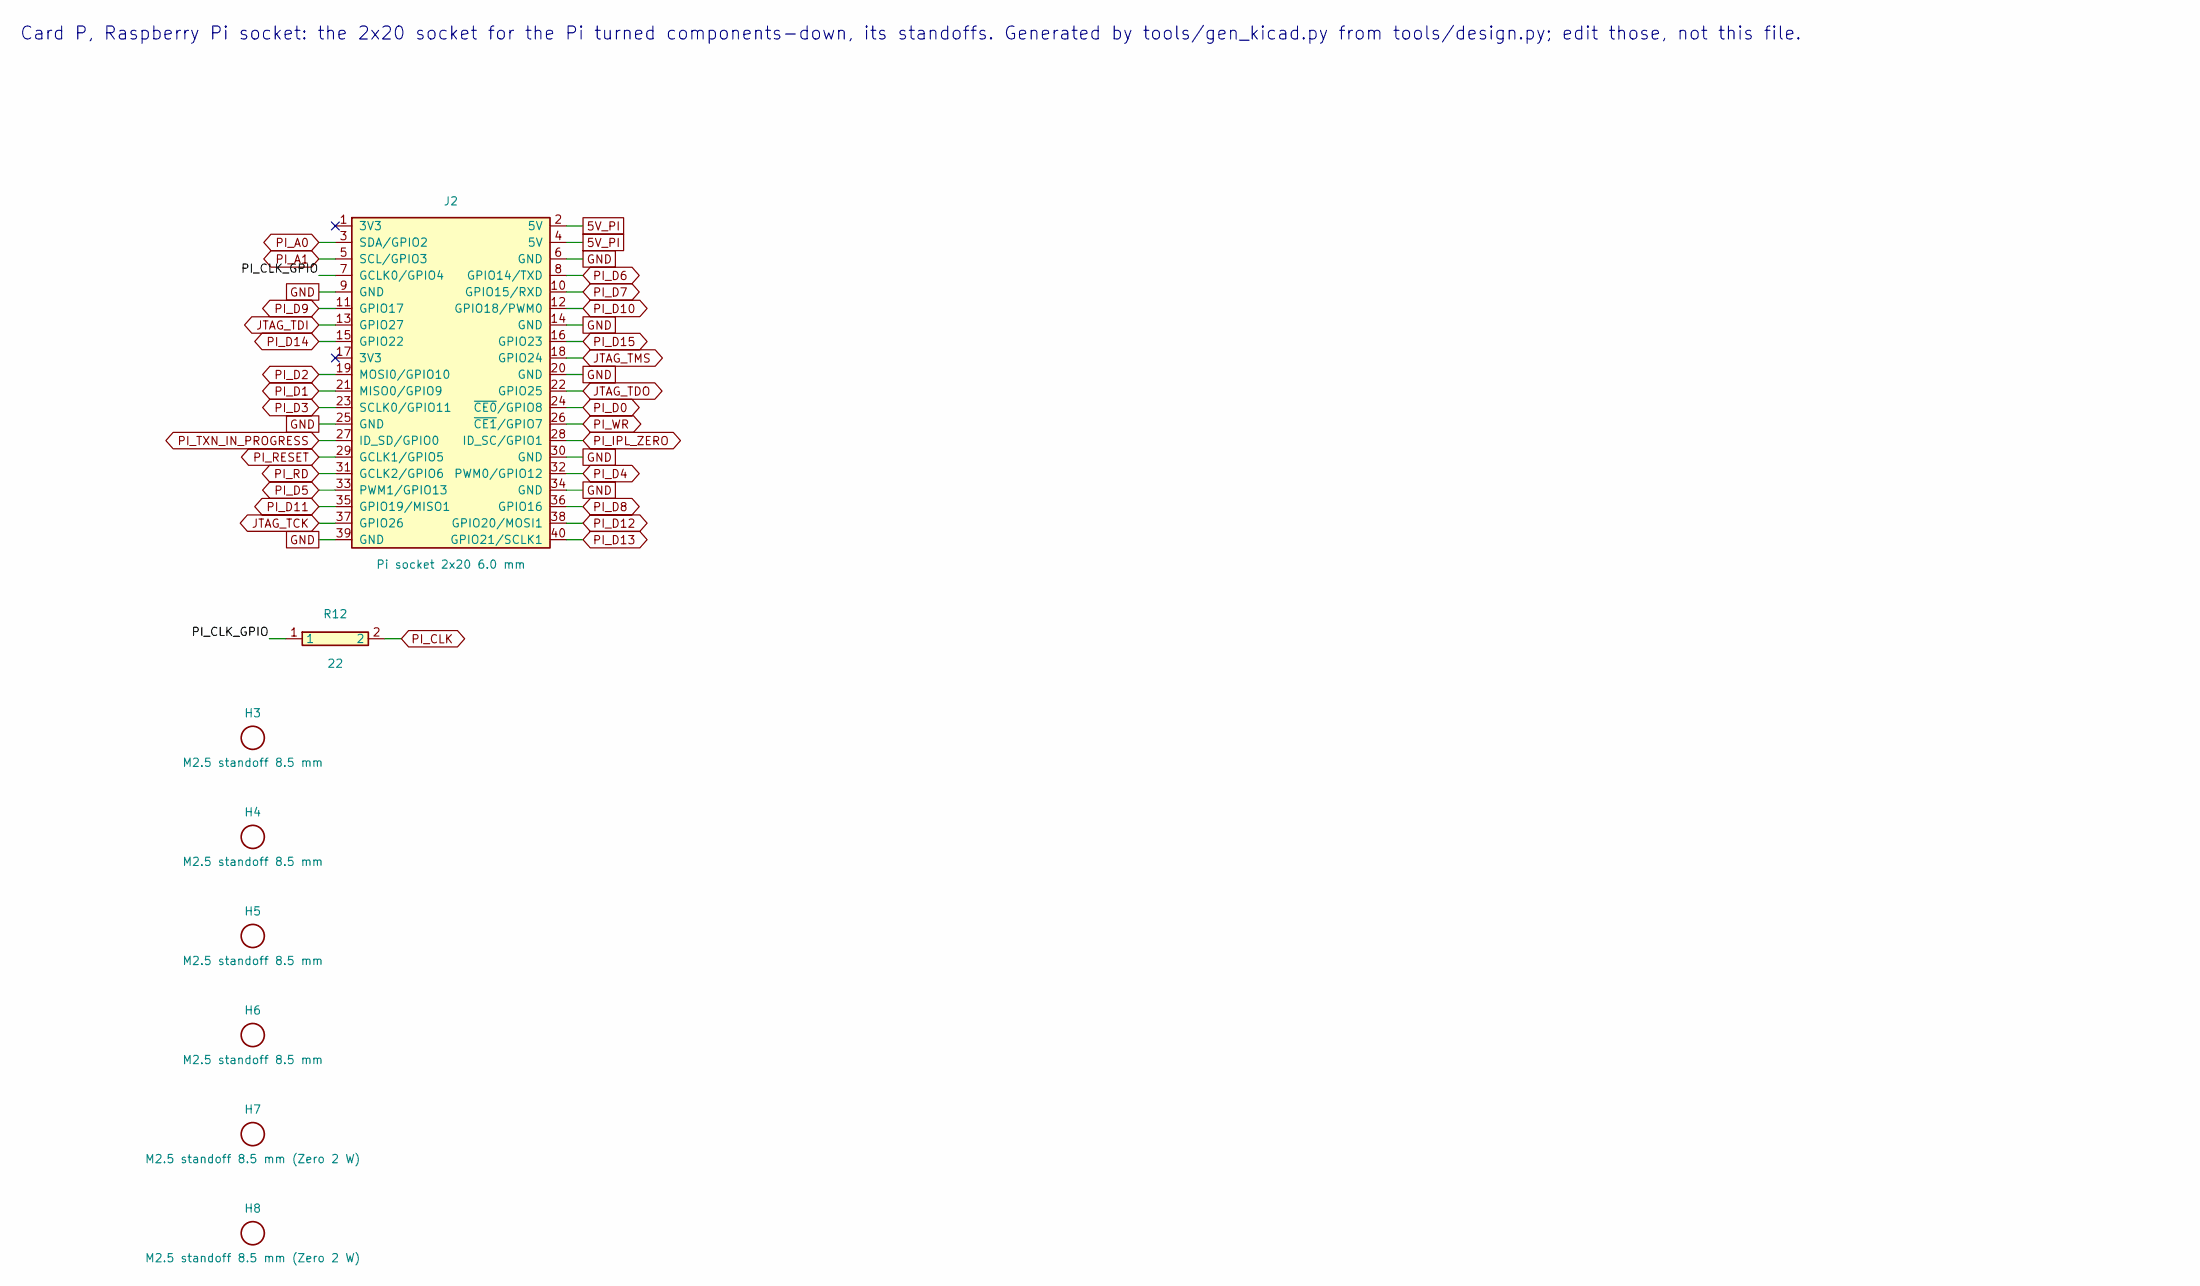
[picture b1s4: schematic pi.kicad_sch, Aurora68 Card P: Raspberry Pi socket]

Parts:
H3, H4, H5, H6: M2.5 standoff 8.5 mm; Aurora68_PiStandoff_M2.5
H7, H8: M2.5 standoff 8.5 mm (Zero 2 W); Aurora68_PiStandoff_M2.5
J2: Pi socket 2x20 6.0 mm; Aurora68_PiSocket_2x20_Inverted; MPN 2x20 female socket, 2.54 mm, 6.0 mm bod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
R12: 22; R_0603_1608Metric; LCSC C23345

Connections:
5V_PI: J2.2, J2.4; also elsewhere on the board
GND: J2.6, J2.9, J2.14, J2.20, J2.25, J2.30, J2.34, J2.39; also elsewhere on the board
JTAG_TCK: J2.37; also elsewhere on the board
JTAG_TDI: J2.13; also elsewhere on the board
JTAG_TDO: J2.22; also elsewhere on the board
JTAG_TMS: J2.18; also elsewhere on the board
PI_A0: J2.3; also elsewhere on the board
PI_A1: J2.5; also elsewhere on the board
PI_CLK: R12.2; also elsewhere on the board
PI_CLK_GPIO: J2.7, R12.1
PI_D0: J2.24; also elsewhere on the board
PI_D1: J2.21; also elsewhere on the board
PI_D2: J2.19; also elsewhere on the board
PI_D3: J2.23; also elsewhere on the board
PI_D4: J2.32; also elsewhere on the board
PI_D5: J2.33; also elsewhere on the board
PI_D6: J2.8; also elsewhere on the board
PI_D7: J2.10; also elsewhere on the board
PI_D8: J2.36; also elsewhere on the board
PI_D9: J2.11; also elsewhere on the board
PI_D10: J2.12; also elsewhere on the board
PI_D11: J2.35; also elsewhere on the board
PI_D12: J2.38; also elsewhere on the board
PI_D13: J2.40; also elsewhere on the board
PI_D14: J2.15; also elsewhere on the board
PI_D15: J2.16; also elsewhere on the board
PI_IPL_ZERO: J2.28; also elsewhere on the board
PI_RD: J2.31; also elsewhere on the board
PI_RESET: J2.29; also elsewhere on the board
PI_TXN_IN_PROGRESS: J2.27; also elsewhere on the board
PI_WR: J2.26; also elsewhere on the board

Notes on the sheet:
Card P, Raspberry Pi socket: the 2x20 socket for the Pi turned components-down, its standoffs. Generated by tools/gen_kicad.py from tools/design.py; edit those, not this file.

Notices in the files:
hardware/pds-card/README.md:
Licences and credits:
- **The PiStorm** (github.com/captain-amygdala/pistorm, MIT licence, "Copyright (c) 2021 PiStorm developers"): Card
P's circuit follows the PiStorm Rev B's, and its CPLD design `rtl/aurora68_pds.v` is derived from the PiStorm's
`rtl/pistorm.v` (Claude Schwarz 2020, Niklas Ekstrom's Verilog rewrite 2020); the MIT notice is kept in that file,
which stays MIT, as do `rtl/aurora68_pds.qsf` and `.sdc`. Thanks to the PiStorm developers.
- **Frimples' MacSE-PiStorm-DirectSocket** (reference/MacSE-PiStorm-DirectSocket): its synchronised /BR and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
